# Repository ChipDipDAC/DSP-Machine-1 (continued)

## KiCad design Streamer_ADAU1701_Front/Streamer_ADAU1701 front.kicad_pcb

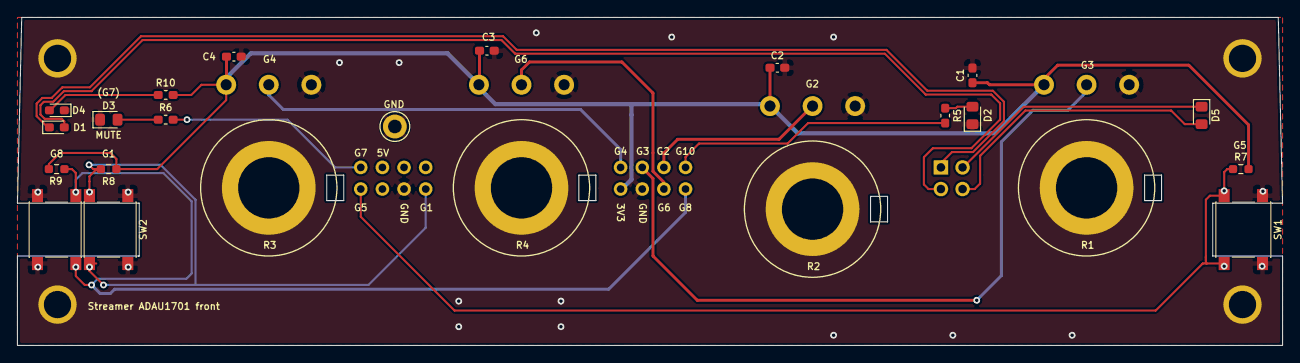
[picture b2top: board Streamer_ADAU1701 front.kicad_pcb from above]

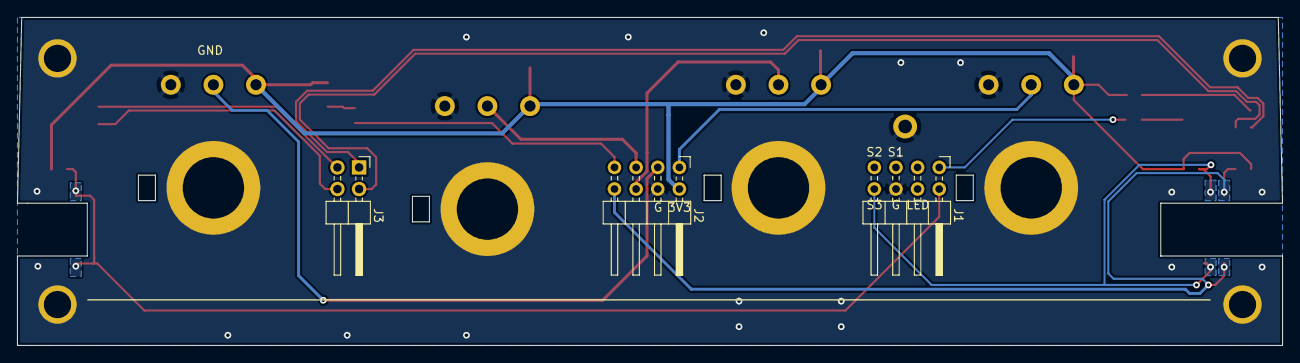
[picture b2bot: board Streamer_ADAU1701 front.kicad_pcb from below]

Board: 2 copper layers, 148.5 x 38.5 mm, 25 parts (3 on the bottom side), 18 nets.

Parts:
C1, C2, C3, C4: 0.1; C_0603_1608Metric_Pad1.08x0.95mm_HandSolder
D1, D4: LED; LED_0603_1608Metric_Pad1.05x0.95mm_HandSolder
D2, D3, D5: LED; LED_0805_2012Metric_Pad1.15x1.40mm_HandSolder
J1, J2: Conn_02x04_Odd_Even; PinHeader_2x04_P2.54mm_Horizontal
J3: Conn_02x02_Odd_Even; PinHeader_2x02_P2.54mm_Horizontal
R1, R2, R3, R4: R_POT_TRIM; Potentiometer_Piher_PC-16_Single_Vertical
R5, R6, R10: 560R; R_0603_1608Metric_Pad1.05x0.95mm_HandSolder
R7, R8, R9: 10k; R_0603_1608Metric_Pad0.98x0.95mm_HandSolder
SW1, SW2, SW3: SW_Push_Dual; SW_SPST_PTS645

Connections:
CLIP+: D5.2, J3.4
CLIP-: D5.1, J3.3
GND: C1.2, C2.2, C3.2, C4.2, D2.1, D3.1, D4.1, J1.6, J2.4, R1.3, R2.3, R3.3, R4.3, SW1.1, SW2.1, SW3.1
GPIO1_COMP: J1.8, R8.2, SW2.2
GPIO2_BAL: J2.5, R2.2
GPIO3_VOL: J2.3, R1.2
GPIO4_BASS: J2.1, R3.2
GPIO5_MUTE: J1.2, R7.1, SW1.2
GPIO6_TREBLE: J2.6, R4.2
GPIO7\LED_COMP: J1.1, R6.2
GPIO8_SBASS: J2.8, R9.2, SW3.2
GPIO10\LED_MUTE: J2.7, R5.2
unnamed: D2.2, R5.1
unnamed: D3.2, R6.1
unnamed: D4.2, R10.1
SHD+: D1.2, J3.2
SHD-: D1.1, J3.1
VDD: C1.1, C2.1, C3.1, C4.1, J2.2, R1.1, R2.1, R3.1, R4.1, R7.2, R8.1, R9.1, R10.2

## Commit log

2022-04-21 SigmaStudio & ChipStudio projects
